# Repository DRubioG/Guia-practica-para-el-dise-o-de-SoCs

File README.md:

# Guia práctica para el diseño de SoCs

Este es mi proyecto de final de carrera

## [Documentos](/Documentos/)

En esta carpeta se ubica el documento de mi trabajo de final de carrera

## [Zynq7000](/esquematico_Zynq_7000/)

Estos son los planos de la Zynq7000

## [Zynq-UltraScale+](/esquematico_Zynq-UltraScale/esquematico_Zynq-UltraScale/)

Estos son los planos de la Zynq-UltraScale+

## [Ficheros de configuración](/Ficheros_configuracion/)

Estos son los ficheros de confguración, además de los ficheros XDC

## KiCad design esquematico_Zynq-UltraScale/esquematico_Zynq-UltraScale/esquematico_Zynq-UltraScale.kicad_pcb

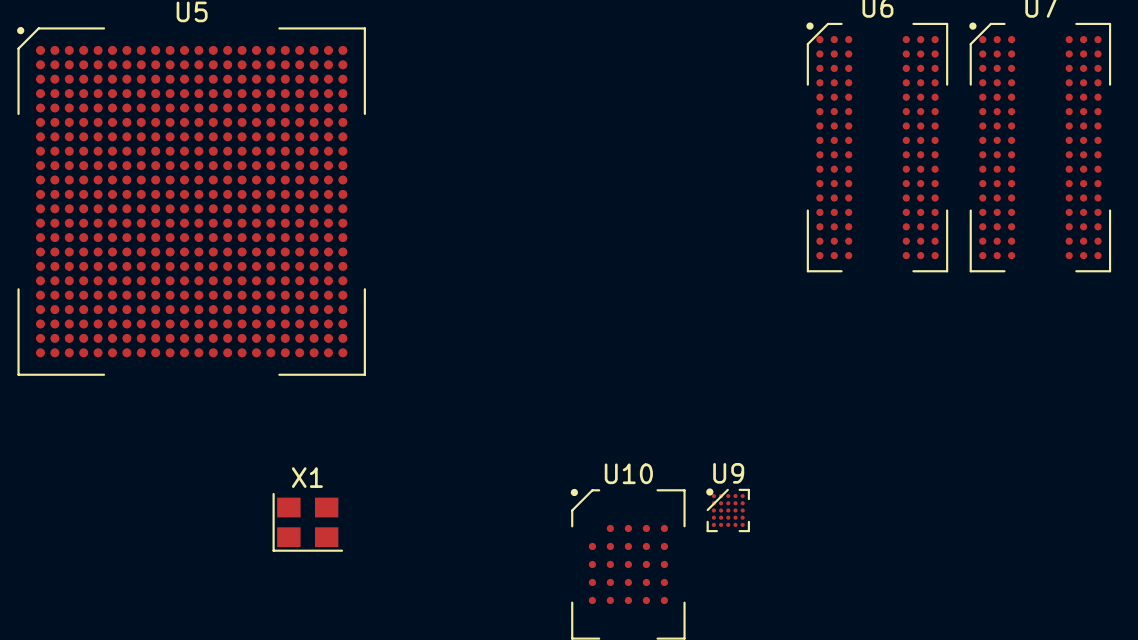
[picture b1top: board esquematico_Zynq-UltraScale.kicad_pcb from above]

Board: 2 copper layers, 6 parts (0 on the bottom side), 52 nets, no tracks yet.

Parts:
U5: XCZU2CG; SBVA484
U6, U7: MT40A512M16; FBGA96_LY
U9: IP4856CX25; BGA-25_5x5_2.049999x2.049999mm
U10: MT25QU512ABB; BGA-25_5x5_6.0x8.0mm
X1: ASE-xxxMHz; Oscillator_SMD_Abracon_ASE-4Pin_3.2x2.5mm

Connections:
+0V85: U5.F19, U5.H7, U5.H8, U5.H10, U5.H19, U5.J7, U5.J9, U5.J11, U5.K8, U5.K19, U5.L7, U5.L11, U5.M7, U5.M8, U5.N7, U5.N11, U5.N12, U5.N13, U5.N14, U5.N17, U5.P8, U5.P10, U5.P12, U5.P13, U5.P17, U5.R6, U5.R7, U5.R9, U5.R11, U5.R13, U5.R14, U5.R15, U5.R16, U5.T6, U5.T12, U5.T13, U5.T14, U5.T16, U5.T17
+1V2: U5.AB18, U5.M14, U5.M15, U5.P19, U5.T20, U5.V16, U5.V21, U5.Y17, U5.Y22, U6.A1, U6.A9, U6.B3, U6.B9, U6.C1, U6.D1, U6.D9, U6.F2, U6.F8, U6.G1, U6.G7, U6.G9, U6.J1, U6.J2, U6.J8, U6.J9, U6.L1, U6.L9, U6.R1, U6.T9, U7.A1, U7.A9, U7.B3, U7.B9, U7.C1, U7.D1, U7.D9, U7.F2, U7.F8, U7.G1, U7.G7, U7.G9, U7.J1, U7.J2, U7.J8, U7.J9, U7.L1, U7.L9, U7.R1, U7.T9
+1V8: U5.A21, U5.AA5, U5.B19, U5.C4, U5.C11, U5.C16, U5.D14, U5.D19, U5.F10, U5.G13, U5.H16, U5.J6, U5.K5, U5.K6, U5.L6, U5.L13, U5.L14, U5.L16, U5.L17, U5.M6, U5.M12, U5.M16, U5.M17, U5.M20, U5.P6, U5.V6, U9.B3, U9.C2, U10.B4
+2V5: U6.B1, U6.R9, U7.B1, U7.R9
+3V3: U5.B3, U5.B8, U5.E7, U5.G3, U5.K2, U5.P4, U9.A4, U9.C4, X1.4
/DDr/DDR_A0: U5.AA22, U5.U16, U5.U17, U5.V17, U5.W18, U6.P3, U7.P3
/DDr/DDR_A1: U5.AB20, U6.P7, U7.P7
/DDr/DDR_A2: U5.AB17, U6.R3, U7.R3
/DDr/DDR_A3: U5.AB19, U6.N7, U7.N7
/DDr/DDR_A4: U5.AB21, U6.N3, U7.N3
/DDr/DDR_A5: U5.AB16, U6.P8, U7.P8
/DDr/DDR_A6: U5.Y20, U6.P2, U7.P2
/DDr/DDR_A7: U5.Y19, U6.R8, U7.R8
/DDr/DDR_A8: U5.W17, U6.R2, U7.R2
/DDr/DDR_A9: U5.Y18, U6.R7, U7.R7
/DDr/DDR_A10: U5.Y21, U6.M3, U7.M3
/DDr/DDR_A11: U5.AA21, U6.T2, U7.T2
/DDr/DDR_A12: U5.AA18, U6.M7, U7.M7
/DDr/DDR_A13: U5.AA19, U6.T8, U7.T8
/DDr/DDR_A14: U5.AA17, U6.L2, U7.L2
/DDr/DDR_A15: U5.AA16, U6.M8, U7.M8
/DDr/DDR_A16: U5.Y16, U6.L8, U7.L8
/DDr/DDR_ACT: U5.T21, U5.U15, U5.U19, U5.U22, U5.V20, U5.V22, U5.W20, U5.W22, U6.K2, U6.K3, U6.L3, U6.L7, U6.P9, U6.T3, U7.K2, U7.K3, U7.K7, U7.K8, U7.L3, U7.L7, U7.P9, U7.T3
/DDr/DDR_BA0: U6.N2, U7.N2
/DDr/DDR_BA1: U6.N8, U7.N8
/DDr/DDR_BG0: U6.M2, U7.M2
/DDr/DDR_DQS_N0: U6.F3, U7.F3
/DDr/DDR_DQS_N1: U6.A7, U7.A7
/DDr/DDR_DQS_P0: U6.G3, U7.G3
/DDr/DDR_DQS_P1: U6.B7, U7.B7
/DDr/DDR_RESETN: U5.T18, U6.P1, U7.P1
/MIO & REFERENCIA/CS: U5.AA1, U10.C2
/MIO & REFERENCIA/IO0: U5.U6, U10.D3
/MIO & REFERENCIA/IO1: U5.W1, U10.D2
/MIO & REFERENCIA/IO2: U5.V2, U10.C4
/MIO & REFERENCIA/IO3: U5.U5, U10.D4
/MIO & REFERENCIA/MIO_CD: U5.A11, U9.D3
/MIO & REFERENCIA/MIO_CLK_IN: U5.C13, U9.C1
/MIO & REFERENCIA/MIO_CMD: U5.A13, U9.D2
/MIO & REFERENCIA/MIO_DAT0: U5.C12, U9.D1
/MIO & REFERENCIA/MIO_DAT1: U5.B12, U9.E1
/MIO & REFERENCIA/MIO_DAT2: U5.A12, U9.A1
/MIO & REFERENCIA/MIO_DAT3: U5.D13, U9.B1
/MIO & REFERENCIA/MIO_DIR0: U5.B10, U9.A3
/MIO & REFERENCIA/MIO_DIR1_3: U5.D12, U9.E3
/MIO & REFERENCIA/MIO_DIR_CMD: U5.D11, U9.A2
/MIO & REFERENCIA/MIO_SEL: U5.C10, U9.B2
/MIO & REFERENCIA/MIO_WP: U5.B11, U9.E4
/MIO & REFERENCIA/PS_CLK: U5.H14, X1.3
/MIO & REFERENCIA/SCK: U5.U4, U10.B2
GND: U5.A1, U5.A5, U5.A10, U5.A15, U5.A18, U5.A22, U5.AA10, U5.AA15, U5.AA20, U5.AB1, U5.AB3, U5.AB8, U5.AB13, U5.AB22, U5.B13, U5.B20, U5.C1, U5.C6, U5.C18, U5.C21, U5.C22, U5.D4, U5.D9, U5.D20, U5.E2, U5.E12, U5.E17, U5.E18, U5.E21, U5.E22, U5.F5, U5.F15, U5.F20, U5.G8, U5.G18, U5.G21, U5.G22, U5.H1, U5.H6, U5.H9, U5.H11, U5.H15, U5.H17, U5.H18, U5.H20, U5.J4, U5.J8, U5.J10, U5.J14, U5.J15, U5.J16, U5.J18, U5.J21, U5.J22, U5.K7, U5.K11, U5.K17, U5.K20, U5.L5, U5.L8, U5.L15, U5.L18, U5.L21, U5.L22, U5.M3, U5.M11, U5.M13, U5.M18, U5.M19, U5.N1, U5.N6, U5.N8, U5.N15, U5.N16, U5.N20, U5.N21, U5.N22, U5.P7, U5.P9, U5.P11, U5.P14, U5.R2, U5.R8, U5.R10, U5.R12, U5.R17, U5.R22, U5.T5, U5.T11, U5.T15, U5.U3, U5.U8, U5.U13, U5.U18, U5.V1, U5.V11, U5.W4, U5.W9, U5.W14, U5.W19, U5.Y2, U5.Y7, U5.Y12, U6.A2, U6.A8, U6.B2, U6.C9, U6.D2, U6.D8, U6.E1, U6.E3, U6.E8, U6.E9, U6.F1, U6.G8, U6.H1, U6.H9, U6.K1, U6.K9, U6.M9, U6.N1, U6.N9, U6.T1, U7.A2, U7.A8, U7.B2, U7.C9, U7.D2, U7.D8, U7.E1, U7.E3, U7.E8, U7.E9, U7.F1, U7.G8, U7.H1, U7.H9, U7.K1, U7.K9, U7.M9, U7.N1, U7.N9, U7.T1, U9.B4, U9.C3, U10.B3, X1.2
unnamed: U10.A2, U10.A3, U10.A4, U10.A5, U10.B1, U10.B5, U10.C1, U10.C3, U10.C5, U10.D1, U10.D5, U10.E1, U10.E2, U10.E3, U10.E5

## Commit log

2023-08-31 update
    New version of the document
